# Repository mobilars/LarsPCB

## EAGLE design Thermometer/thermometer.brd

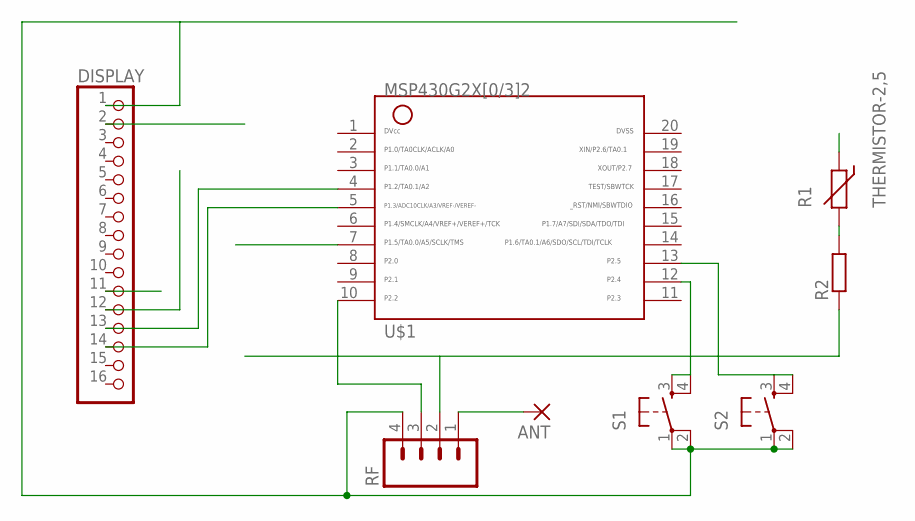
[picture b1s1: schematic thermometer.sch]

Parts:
ANT: 2,54/0,9
DISPLAY: PINHD-1X16; 1X16
R1: THERMISTOR-2,5; RS-2,5
R2: R-EU_0207/10; 0207/10
RF: M04PTH; 1X04
S1, S2: TAC_SWITCHPTH; TACTILE-PTH
U$1: G2X[0/3]2---N20; N20

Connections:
GND: DISPLAY.1, RF.4, S1.1, S1.2, S2.1, S2.2
unnamed: DISPLAY.14, U$1.5
unnamed: DISPLAY.13, U$1.4
unnamed: S2.3, S2.4, U$1.13
unnamed: R2.1, RF.2
unnamed: R1.2, R2.2
unnamed: S1.3, S1.4, U$1.12
unnamed: RF.3, U$1.10
unnamed: ANT.1, RF.1

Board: 2 copper layers, 8 parts (0 on the bottom side), 9 nets, no tracks yet.

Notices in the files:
parts and their libraries:
SparkFun-Electromechanical: Licensing: CC v3.0 Share-Alike You are welcome to use this library for commercial purposes.
